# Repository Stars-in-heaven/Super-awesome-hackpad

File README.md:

# Nano_Flux
I am absolutely horrible with github, sorry if there is something wrong with this repository. But anyways<br> this this is a hackpad i've worked on for like a week?<br>

<b>FEATURES :</b>

*✩ ‎ ‎ Shortcut Modes (switch between)*<br>
*✩ ‎ ‎ 4 macros*<br>
*✩ ‎ ‎ OLED screen displaying mode and<br> ‎ ‎ ‎ ‎‎ ‎ ‎  volume adjustments*<br>
*✩ ‎ ‎ A button to change mode*<br>
*✩ ‎ ‎ star cutout for the PCB to show through*<br>
*✩ ‎ ‎ Rotary encoder (adjusts volume and mutes when pressed)*<br>

----------------------------------------------

| FULLY ASEMBLED|       PCB     |SCHEMATIC   |
| ------------- |:-------------:| ----------:|
|               |               |            |<br>

----------------------------------- 
<br>

<b>BOM:<b><br>
| QUANITYT :        | COMPONENT : |
| ------------- |:-------------:|
| 1      | Seeed XIAO RP2040 |
| 5      | MX-Style switches      |
| 1 | EC11 Rotary encoders      |
|   1    |  0.91 inch OLED display   |
|   5    |   white blank DSA keycaps  |
|    4   |   pos+neg magnets <br> (sourced by myself)  |
<br>

----------
## EXTRA NOTES :
Apart from coding the firmware i'm an entire newbie to CAD, so this was
<br> 
definetely a learning experience. And I definetely picked up a lot while
<br> 
working on this, but that is the entire reason I began working on my hackpad.
<br>
Since I haven't had too much making my own hardware, just wiritng firmware.
<br>
But anyways, The main idea and goal for my hack-pad was to keep it as compact
<br>
and small as possible, while still remaining as functional and useful as possible,
<br>
which is why I added modes, while only having 4 keys (for shortcuts) with the 3
<br>
modes, and counting, you can have over 16 shortcuts all in one tiny macro pad.
<br>
the modes work best when they are for specific tasks, as they keep all the
<br>
specific shortcuts you need in one space. for example, I have one for coding,
<br>
writing notes at school and one for researching. But of course more modes can always
<br>
be added.

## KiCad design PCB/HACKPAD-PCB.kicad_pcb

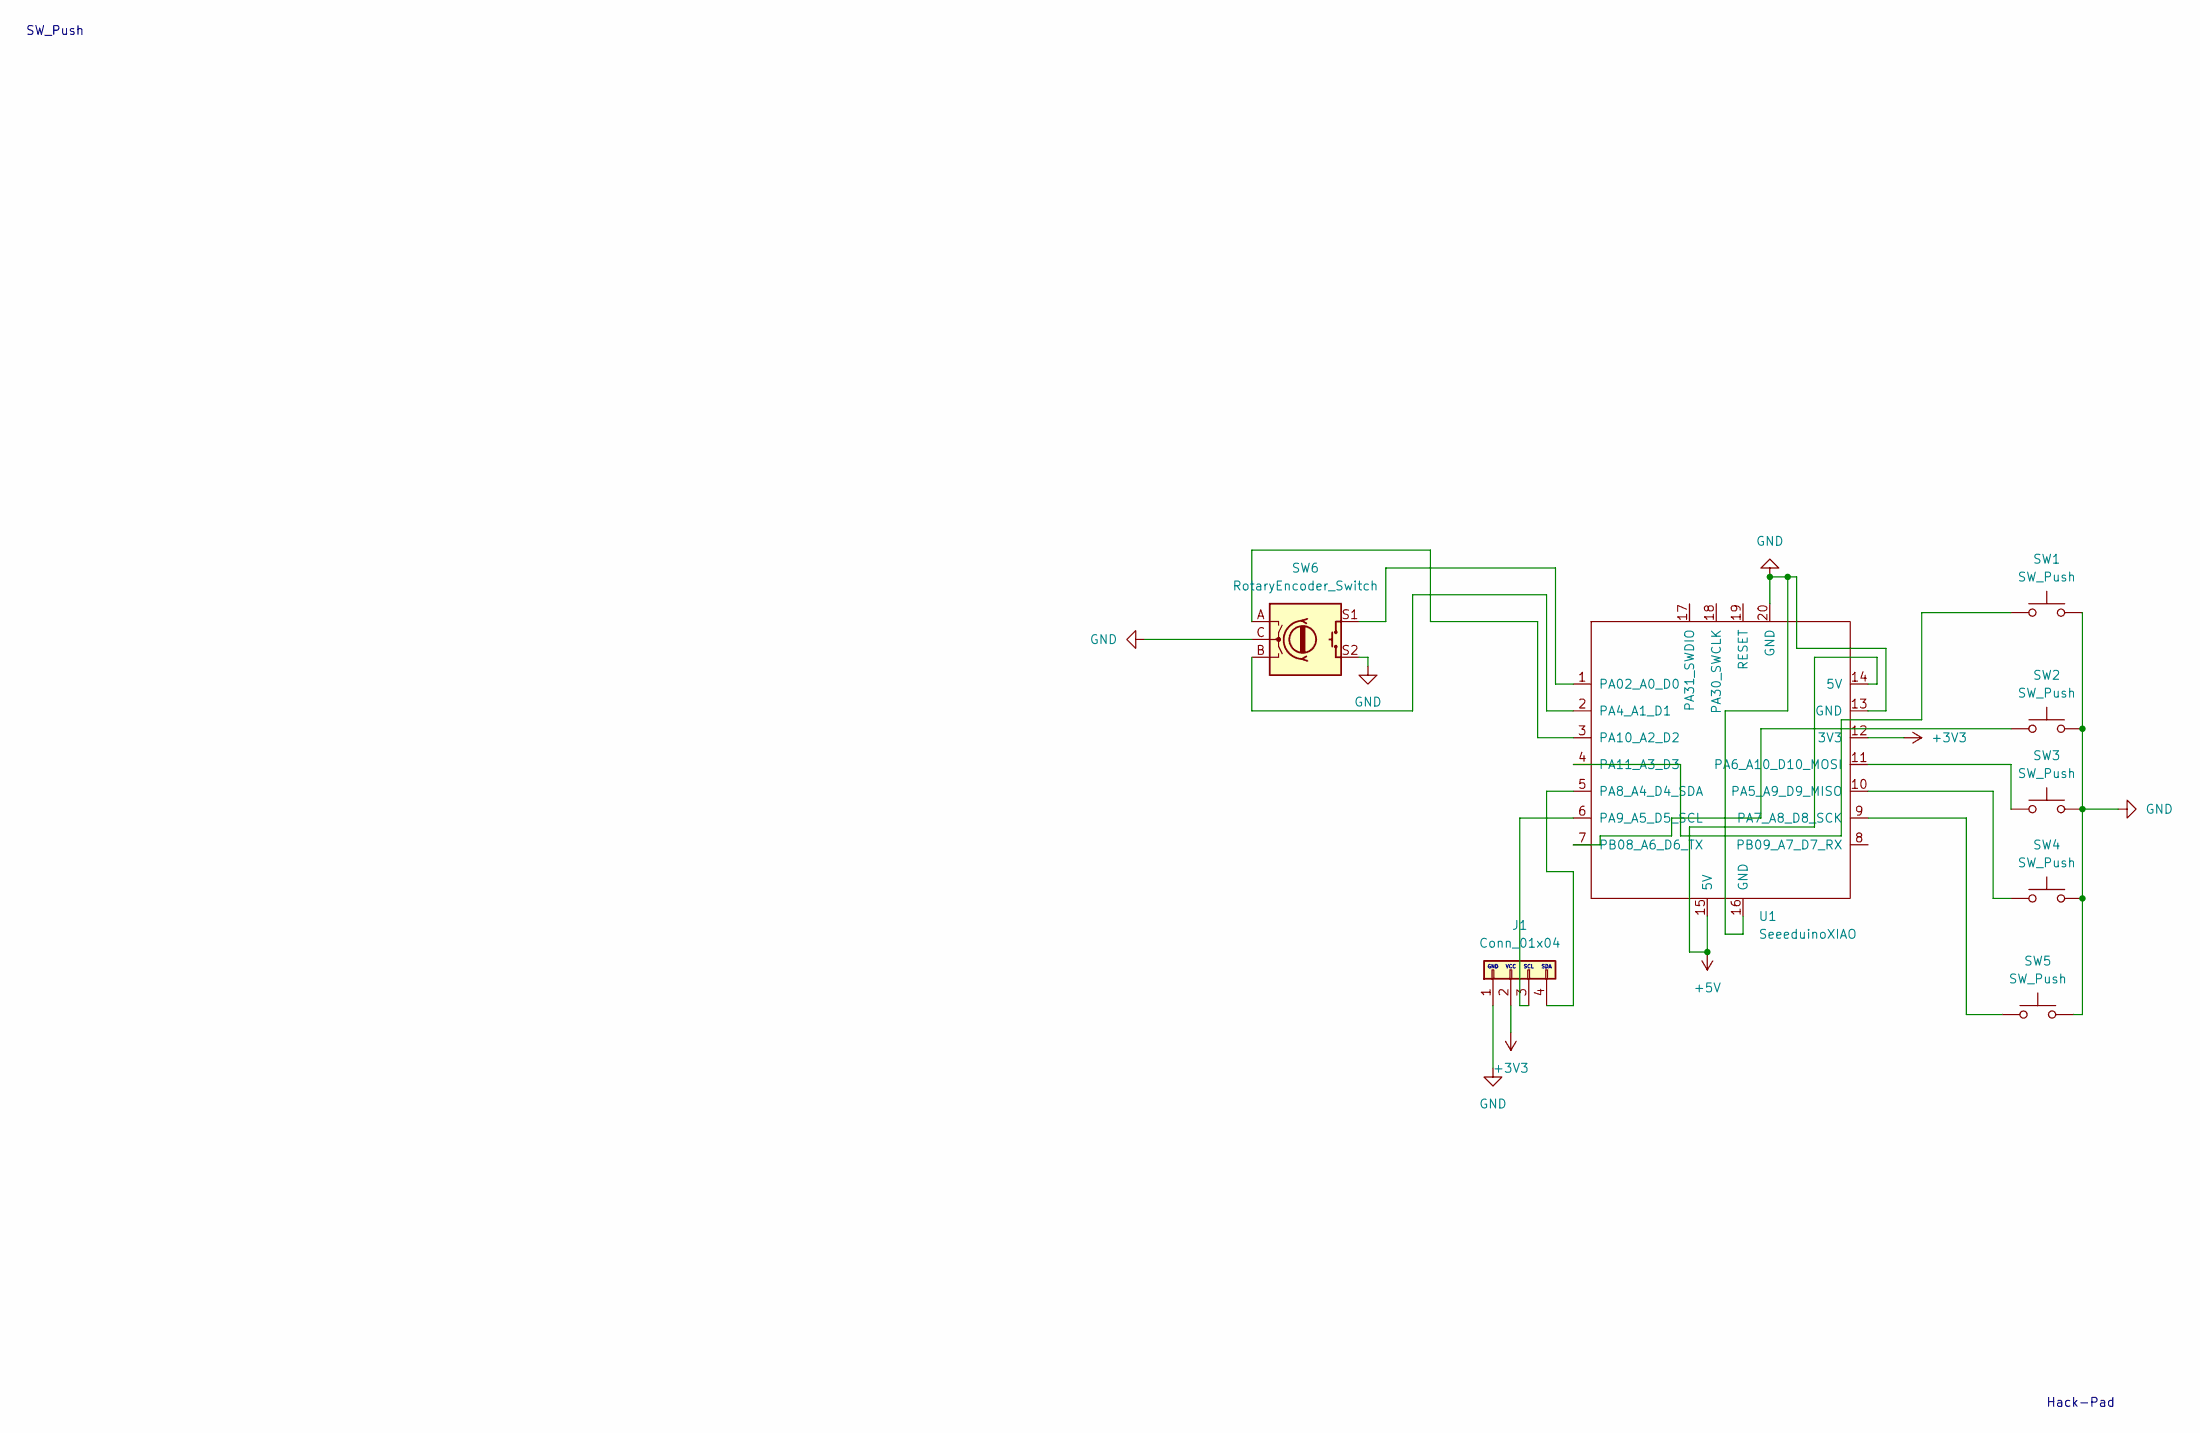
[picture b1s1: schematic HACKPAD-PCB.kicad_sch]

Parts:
J1: Conn_01x04; PinHeader_1x04_P2.54mm_Vertical
SW1, SW2, SW3, SW4, SW5: SW_Push; SW_Cherry_MX_1.00u_PCB
SW6: RotaryEncoder_Switch; RotaryEncoder_Alps_EC11E-Switch_Vertical_H20mm
U1: SeeeduinoXIAO; XIAO-SAMD21-SMD

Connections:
+3V3: J1.2, U1.12 (3V3)
+5V: U1.14 (5V), U1.15 (5V)
GND: J1.1, SW1.2, SW2.2, SW3.2, SW4.2, SW5.2, SW6.C, SW6.S2, U1.13 (GND), U1.16 (GND), U1.20 (GND)
unnamed: J1.3, U1.6 (PA9_A5_D5_SCL)
unnamed: J1.4, U1.5 (PA8_A4_D4_SDA)
unnamed: SW6.S1, U1.1 (PA02_A0_D0)
unnamed: SW6.B, U1.2 (PA4_A1_D1)
unnamed: SW4.1, U1.10 (PA5_A9_D9_MISO)
unnamed: SW3.1, U1.11 (PA6_A10_D10_MOSI)
unnamed: SW5.1, U1.9 (PA7_A8_D8_SCK)
unnamed: SW6.A, U1.3 (PA10_A2_D2)
unnamed: SW1.1, U1.4 (PA11_A3_D3)
unnamed: SW2.1, U1.7 (PB08_A6_D6_TX)

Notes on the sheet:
Hack-Pad
SDA
SW_Push
SCL
VCC
GND

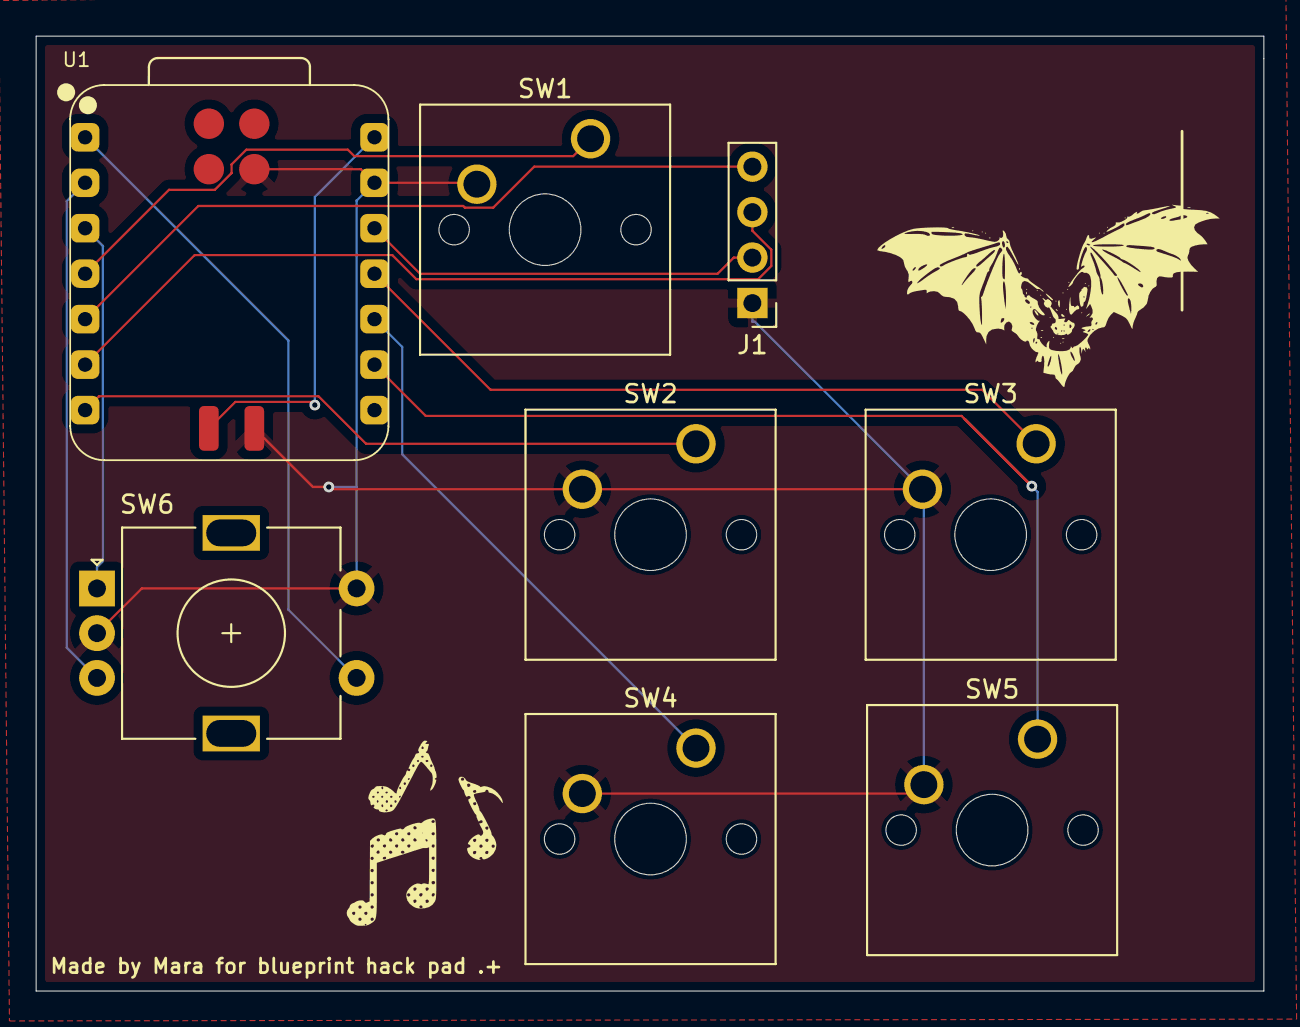
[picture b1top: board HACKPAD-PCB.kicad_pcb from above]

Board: 2 copper layers, 68.6 x 53.3 mm, 10 parts (0 on the bottom side), 13 nets.

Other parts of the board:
.: LOGO
s: LOGO

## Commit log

2026-02-11 Enhance README with images and table
    Added images and a table to the README for better visualization.
2026-02-11 Added all required content to README
    Updated README to improve formatting and clarity.
2026-02-12 added uf2
2026-02-12 firmware
2026-02-12 Add initial .uf2 firmware file
2026-02-12 Update project name in README
    Renamed project from 'Super-awesome-hackpad' to 'Flux-pad'.
2026-02-12 Update project name in README
    Renamed project from 'Flux-pad' to 'Nano_Flux' in README.
2026-02-14 Source file (FCStd)
    for the full macropad with everything together
2026-02-14 Uploaded correct schematic
2026-02-14 added correct pcb after rotating header
2026-02-14 added pro file
2026-02-15 Add filler file to PCB directory
2026-02-15 reuploaded pcb files
2026-02-15 added the custom librarys i used
2026-02-15 zip added with else everything in this folder
2026-02-15 Add fill file with fillrt content
2026-02-19 Removed outdated top half file
2026-02-19 Uploaded correct top half files
